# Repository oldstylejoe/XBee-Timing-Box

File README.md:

# XBee Timing Box

## Goal.

The goal of this timing box is to have low latency, high reliability, and usability in a clinical setting. It must also have sub-millisecond variability in the latency of the pulses.

The XBee (IEEE 802.15.4) protocol fits the bill. It has low latency at about 10.0(1) ms and seems to be reliable in the clinical setting. XBee also has a thriving community, largely driven by its usage in RC drones. A breakout board from SparkFun (Fio V3) already takes care of most of the work. It is mounted on a board (or even a proto-board) and connected to a shift register to give a TTL-type timing pulse.

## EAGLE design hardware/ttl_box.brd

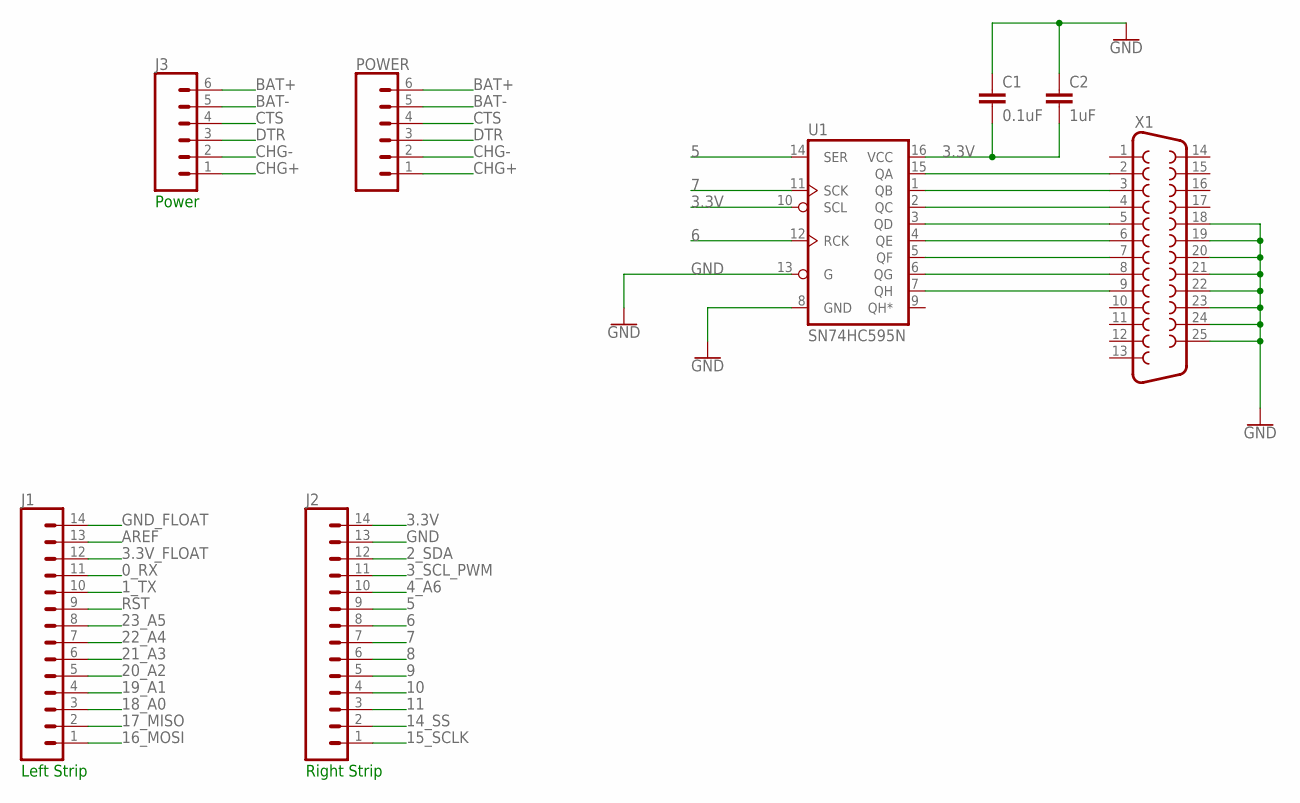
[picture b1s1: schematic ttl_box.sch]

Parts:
C1: 0.1uF; CAP-PTH-SMALL-KIT
C2: 1uF; CAP-PTH-SMALL-KIT
J1, J2: CONN_14; 1X14
J3: CONN_06SILK_FEMALE_PTH; 1X06
POWER: CONN_06SILK_FEMALE_PTH; 1X06
U1: SN74HC595N; DIP16
X1: DB25_FEMALEVB; F25VB

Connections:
0_RX: J1.11
1_TX: J1.10
2_SDA: J2.12
3.3V: C1.2, C2.2, J2.14, U1.10 (SCL), U1.16 (VCC)
3.3V_FLOAT: J1.12
3_SCL_PWM: J2.11
4_A6: J2.10
5: J2.9, U1.14 (SER)
6: J2.8, U1.12 (RCK)
7: J2.7, U1.11 (SCK)
8: J2.6
9: J2.5
10: J2.4
11: J2.3
14_SS: J2.2
15_SCLK: J2.1
16_MOSI: J1.1
17_MISO: J1.2
18_A0: J1.3
19_A1: J1.4
20_A2: J1.5
21_A3: J1.6
22_A4: J1.7
23_A5: J1.8
AREF: J1.13
BAT+: J3.6, POWER.6
BAT-: J3.5, POWER.5
CHG+: J3.1, POWER.1
CHG-: J3.2, POWER.2
CTS: J3.4, POWER.4
DTR: J3.3, POWER.3
GND: C1.1, C2.1, J2.13, U1.8 (GND), U1.13 (G), X1.18, X1.19, X1.20, X1.21, X1.22, X1.23, X1.24, X1.25
GND_FLOAT: J1.14
unnamed: U1.15 (QA), X1.2
unnamed: U1.1 (QB), X1.3
unnamed: U1.2 (QC), X1.4
unnamed: U1.3 (QD), X1.5
unnamed: U1.4 (QE), X1.6
unnamed: U1.5 (QF), X1.7
unnamed: U1.6 (QG), X1.8
unnamed: U1.7 (QH), X1.9
RST: J1.9

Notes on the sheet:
Power
Left Strip
Right Strip

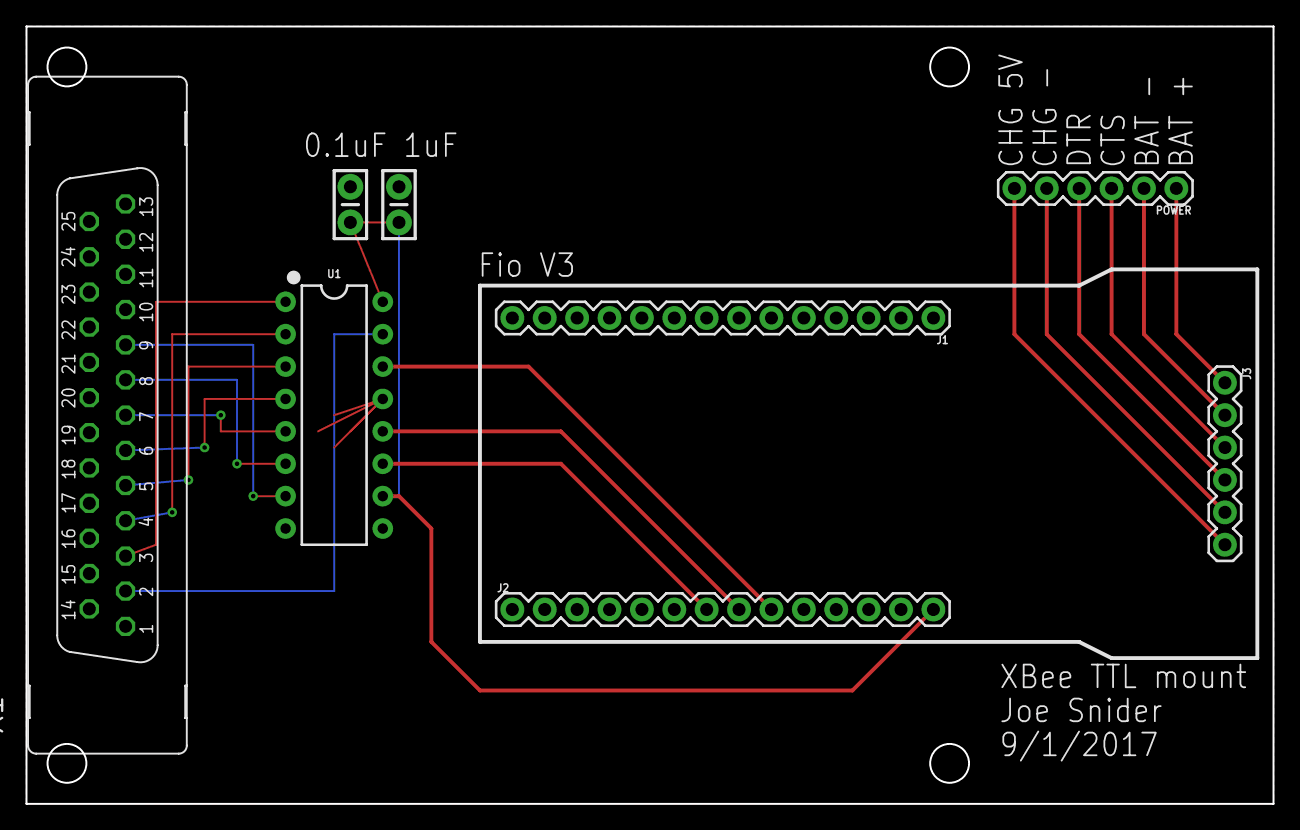
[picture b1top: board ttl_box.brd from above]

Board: 2 copper layers, 97.8 x 61.0 mm, 8 parts (0 on the bottom side), 19 nets.

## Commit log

2017-09-25 first hardware
2018-04-17 uploaded shift register arduino code

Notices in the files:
parts and their libraries:
SparkFun-Capacitors: Licensing: Creative Commons ShareAlike 4.0 International - https://creativecommons.org/licenses/by-sa/4.0
